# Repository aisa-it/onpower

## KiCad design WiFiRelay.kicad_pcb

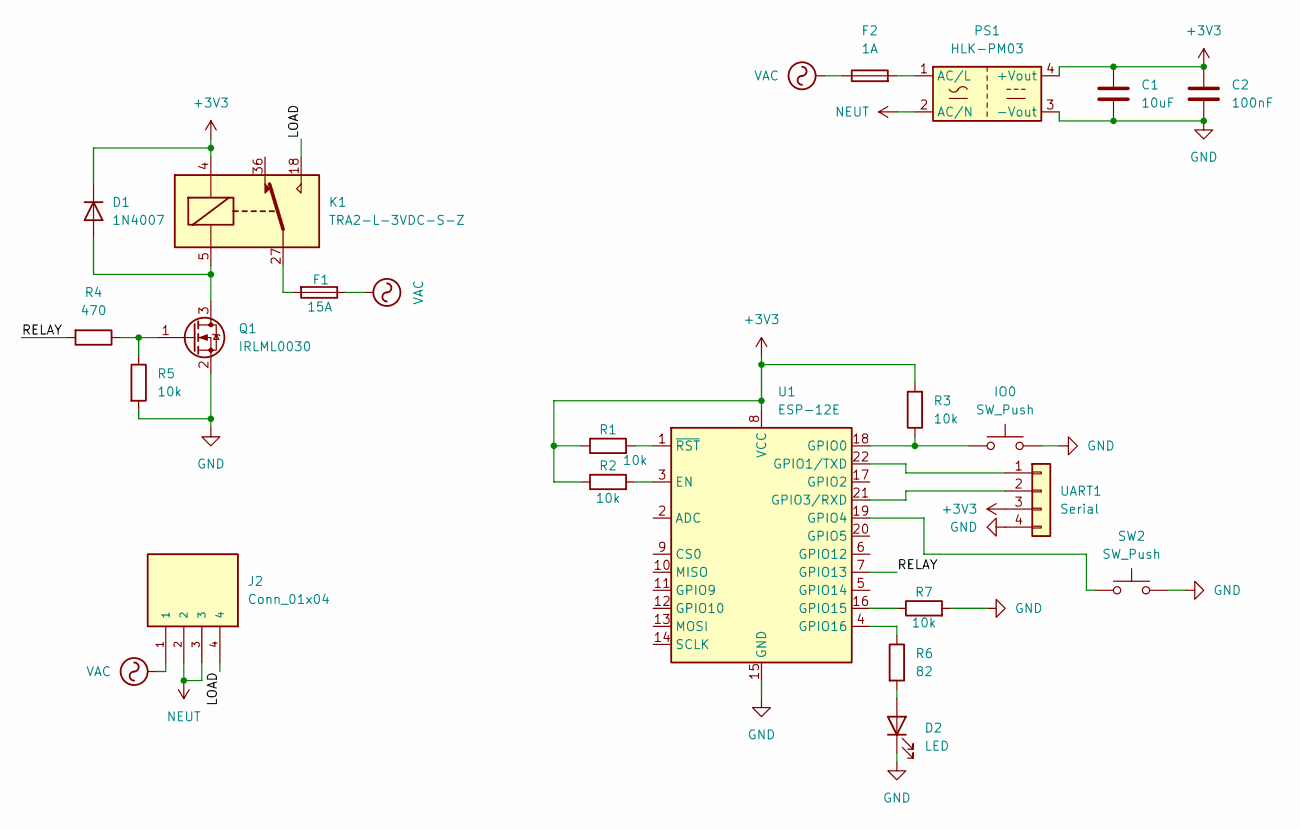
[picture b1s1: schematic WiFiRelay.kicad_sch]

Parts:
C1: 10uF; C_1206_3216Metric_Pad1.33x1.80mm_HandSolder
C2: 100nF; C_1206_3216Metric_Pad1.33x1.80mm_HandSolder
D1: 1N4007; D_A-405_P2.54mm_Vertical_KathodeUp
D2: LED; LED_D3.0mm
F1: 15A; Fuse_Littelfuse_395Series
F2: 1A; Fuse_Littelfuse_395Series
IO0: SW_Push; R_0805_2012Metric_Pad1.20x1.40mm_HandSolder
J2: Conn_01x04; CUI_TBP01R2-508-04BE
K1: TRA2-L-3VDC-S-Z; TRA2
PS1: HLK-PM03; Converter_ACDC_Hi-Link_HLK-PMxx
Q1: IRLML0030; SOT-23
R1, R2, R3, R5, R7: 10k; R_1206_3216Metric_Pad1.30x1.75mm_HandSolder
R4: 470; R_1206_3216Metric_Pad1.30x1.75mm_HandSolder
R6: 82; R_1206_3216Metric_Pad1.30x1.75mm_HandSolder
SW2: SW_Push; PinHeader_1x02_P2.54mm_Vertical
U1: ESP-12E
UART1: Serial; PinHeader_1x04_P2.54mm_Vertical

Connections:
+3V3: C1.1, C2.1, D1.1 (K), K1.4, PS1.4 (+Vout), R1.1, R2.1, R3.2, U1.8 (VCC), UART1.3
/LOAD: J2.4, K1.18
/RELAY: R4.2, U1.7 (GPIO13)
GND: C1.2, C2.2, D2.1 (K), IO0.2, PS1.3 (-Vout), Q1.2 (S), R5.2, R7.2, SW2.2, U1.15 (GND), UART1.4
NEUT: J2.2, J2.3, PS1.2 (AC/N)
unnamed: D1.2 (A), K1.5, Q1.3 (D)
unnamed: D2.2 (A), R6.2
unnamed: F1.2, K1.27
unnamed: F2.2, PS1.1 (AC/L)
unnamed: Q1.1 (G), R4.1, R5.1
unnamed: R2.2, U1.3 (EN)
unnamed: IO0.1, R3.1, U1.18 (GPIO0)
unnamed: U1.22 (GPIO1/TXD), UART1.1
unnamed: U1.21 (GPIO3/RXD), UART1.2
unnamed: SW2.1, U1.19 (GPIO4)
unnamed: R7.1, U1.16 (GPIO15)
unnamed: R6.1, U1.4 (GPIO16)
unnamed: R1.2, U1.1 (~RST)
VAC: F1.1, F2.1, J2.1

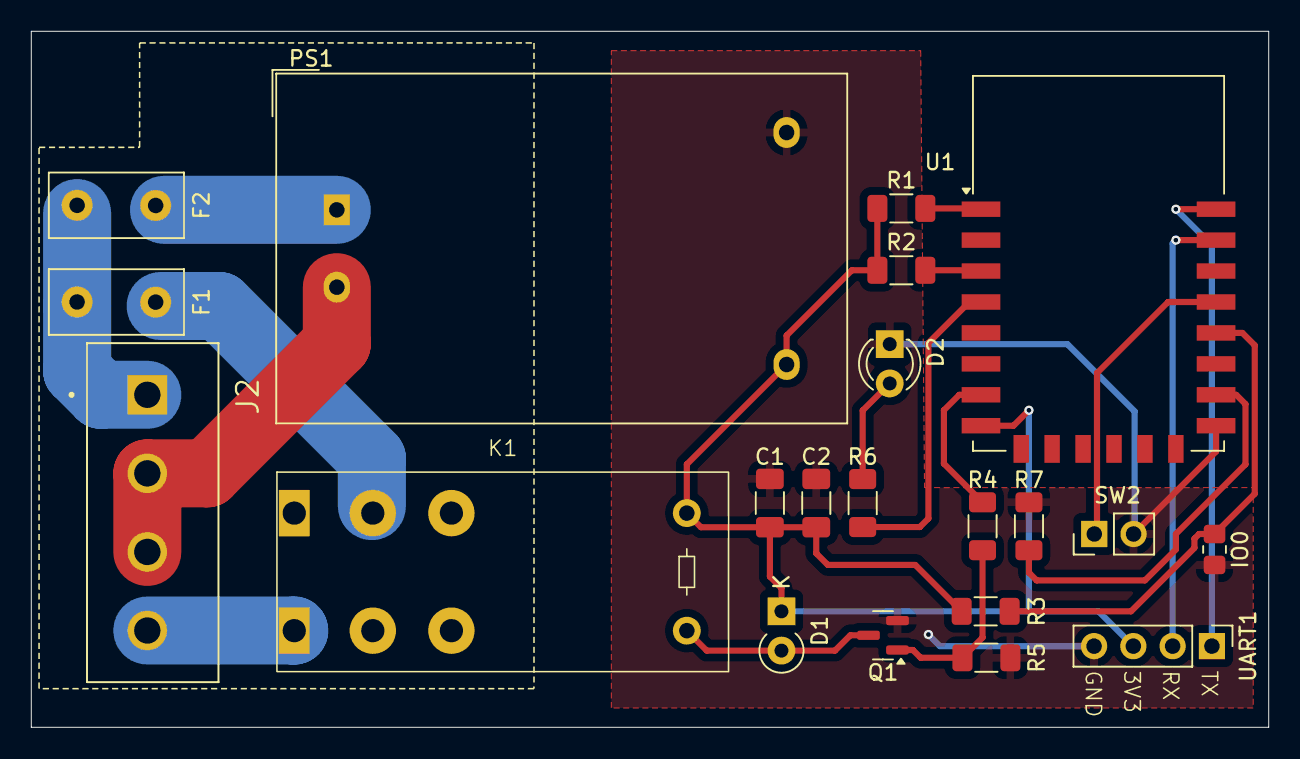
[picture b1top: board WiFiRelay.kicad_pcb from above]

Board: 2 copper layers, 80.0 x 45.0 mm, 21 parts (0 on the bottom side), 19 nets.

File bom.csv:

"Reference","Value","Qty","DNP","Price","Purchase-URL"
"C1","10uF","1","","24","https://www.chipdip.ru/product/grm31cr61a106k"
"C2","100nF","1","","8",""
"D1","1N4007","1","","0,8","https://aliexpress.ru/item/32731035430.html?sku_id=120000180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"
"D2","LED","1","","19","https://www.chipdip.ru/product/l-1154gt"
"F1","15A","1","","44","https://aliexpress.ru/item/1005002933092692.html?sku_id=1200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"
"F2","1A","1","","39","https://www.chipdip.ru/product/mf02s84-1000-1"
"IO0,SW2","SW_Push","2","","-- смешанные значения --",""
"J2","Conn_01x04","1","","33","https://www.chipdip.ru/product/300-041-12"
"K1","TRA2-L-3VDC-S-Z","1","","88","https://www.chipdip.ru/product0/8025423609"
"PS1","HLK-PM03","1","","170",""
"Q1","IRLML0030","1","","19","https://www.chipdip.ru/product0/8017689792"
"R1,R2,R3,R5","10k","4","","0,4",""
"R4","470","1","","0,4",""
"R6","82","1","","0,4",""
"U1","ESP-12E","1","","100",""
"UART1","Serial","1","","",""

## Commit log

2024-05-10 INIT
2024-05-14 release
2024-08-15 fix pins
2024-08-15 case/base.stl: convert to Git LFS
2024-08-15 case/cover.stl: convert to Git LFS
